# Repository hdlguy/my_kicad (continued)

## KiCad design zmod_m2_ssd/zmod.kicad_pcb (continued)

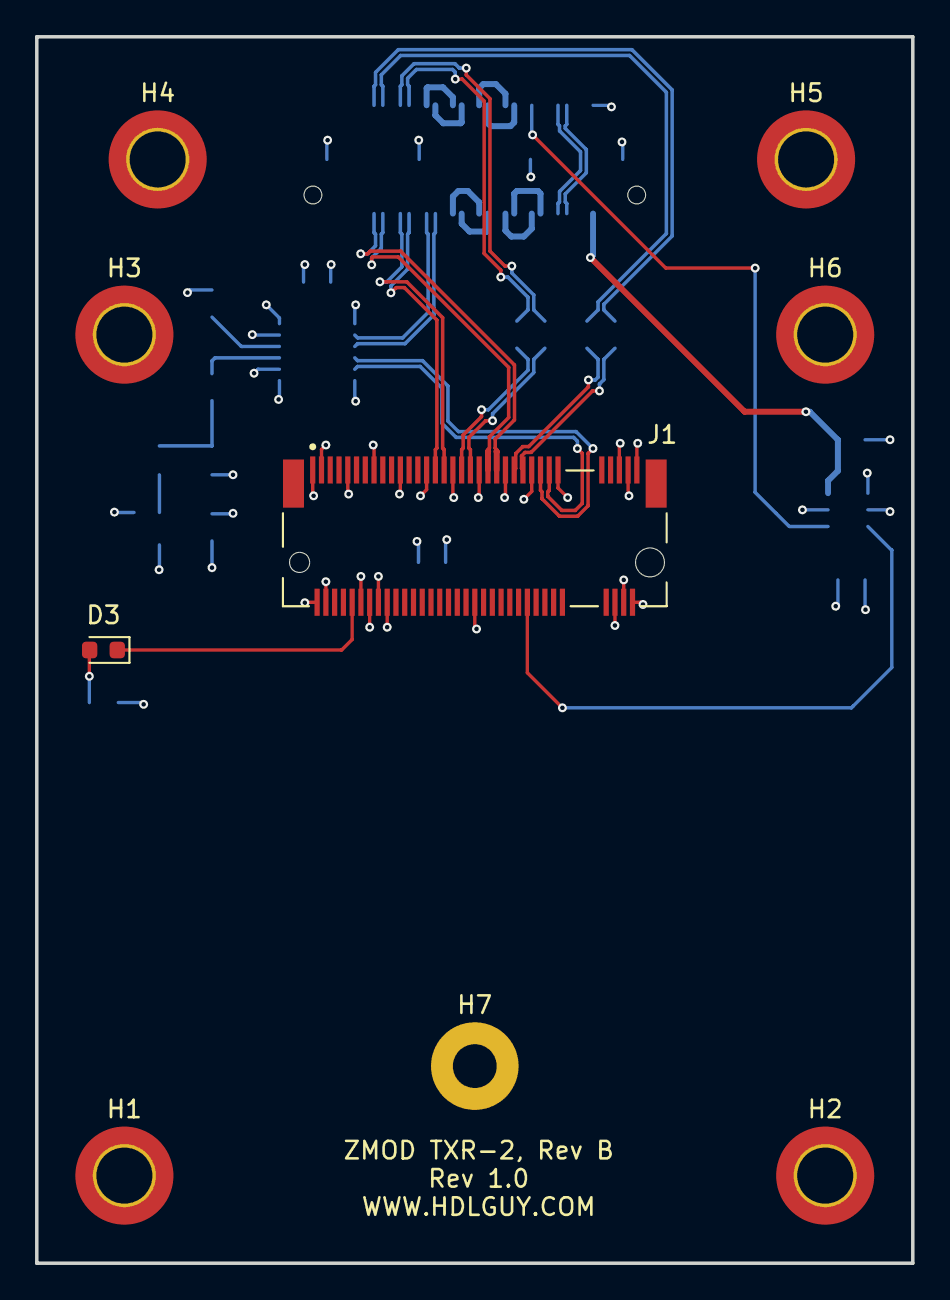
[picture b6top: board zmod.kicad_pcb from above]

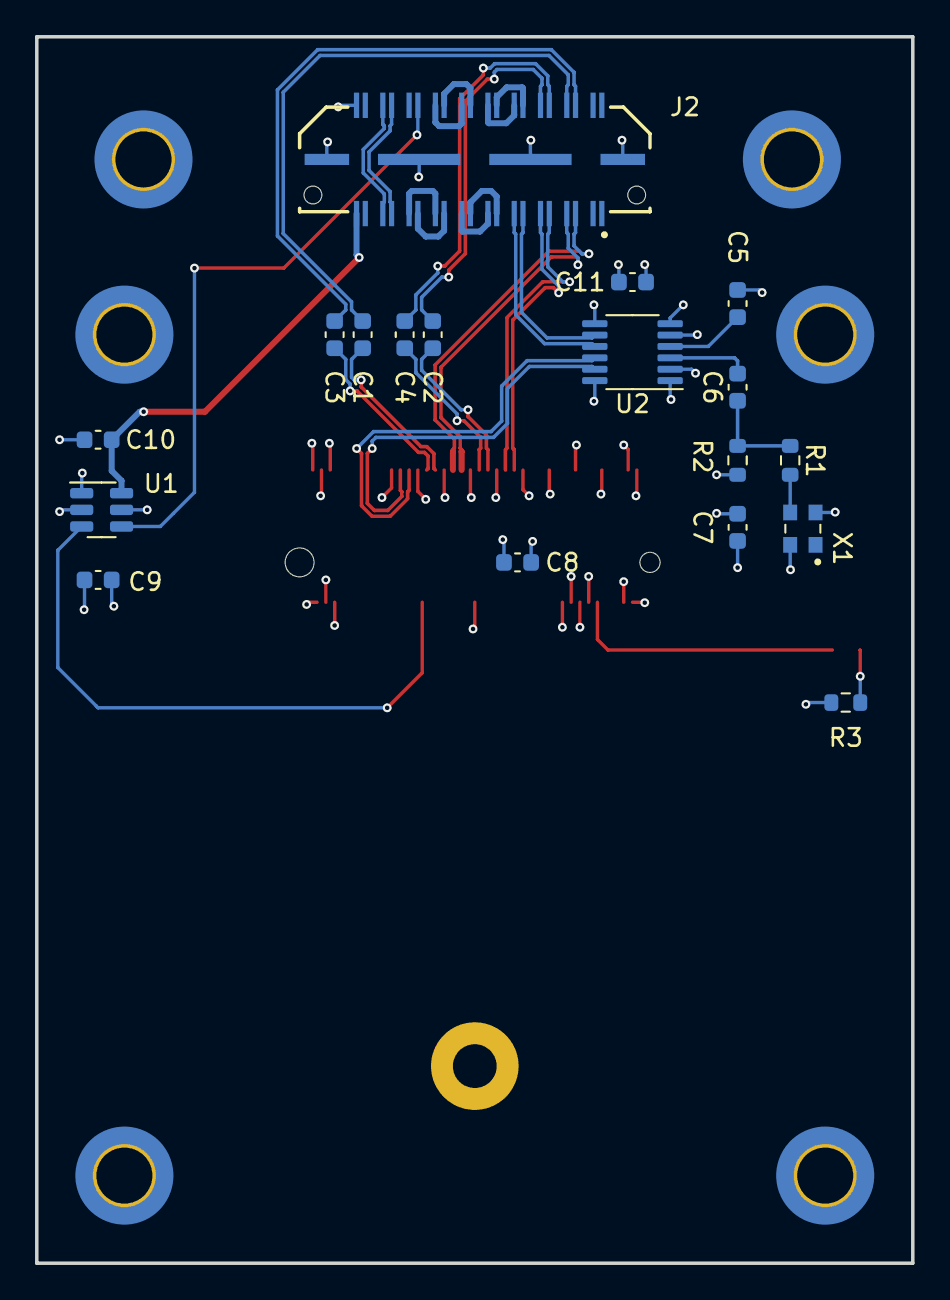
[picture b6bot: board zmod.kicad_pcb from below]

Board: 4 copper layers, 50.0 x 70.0 mm, 27 parts (18 on the bottom side), 37 nets.

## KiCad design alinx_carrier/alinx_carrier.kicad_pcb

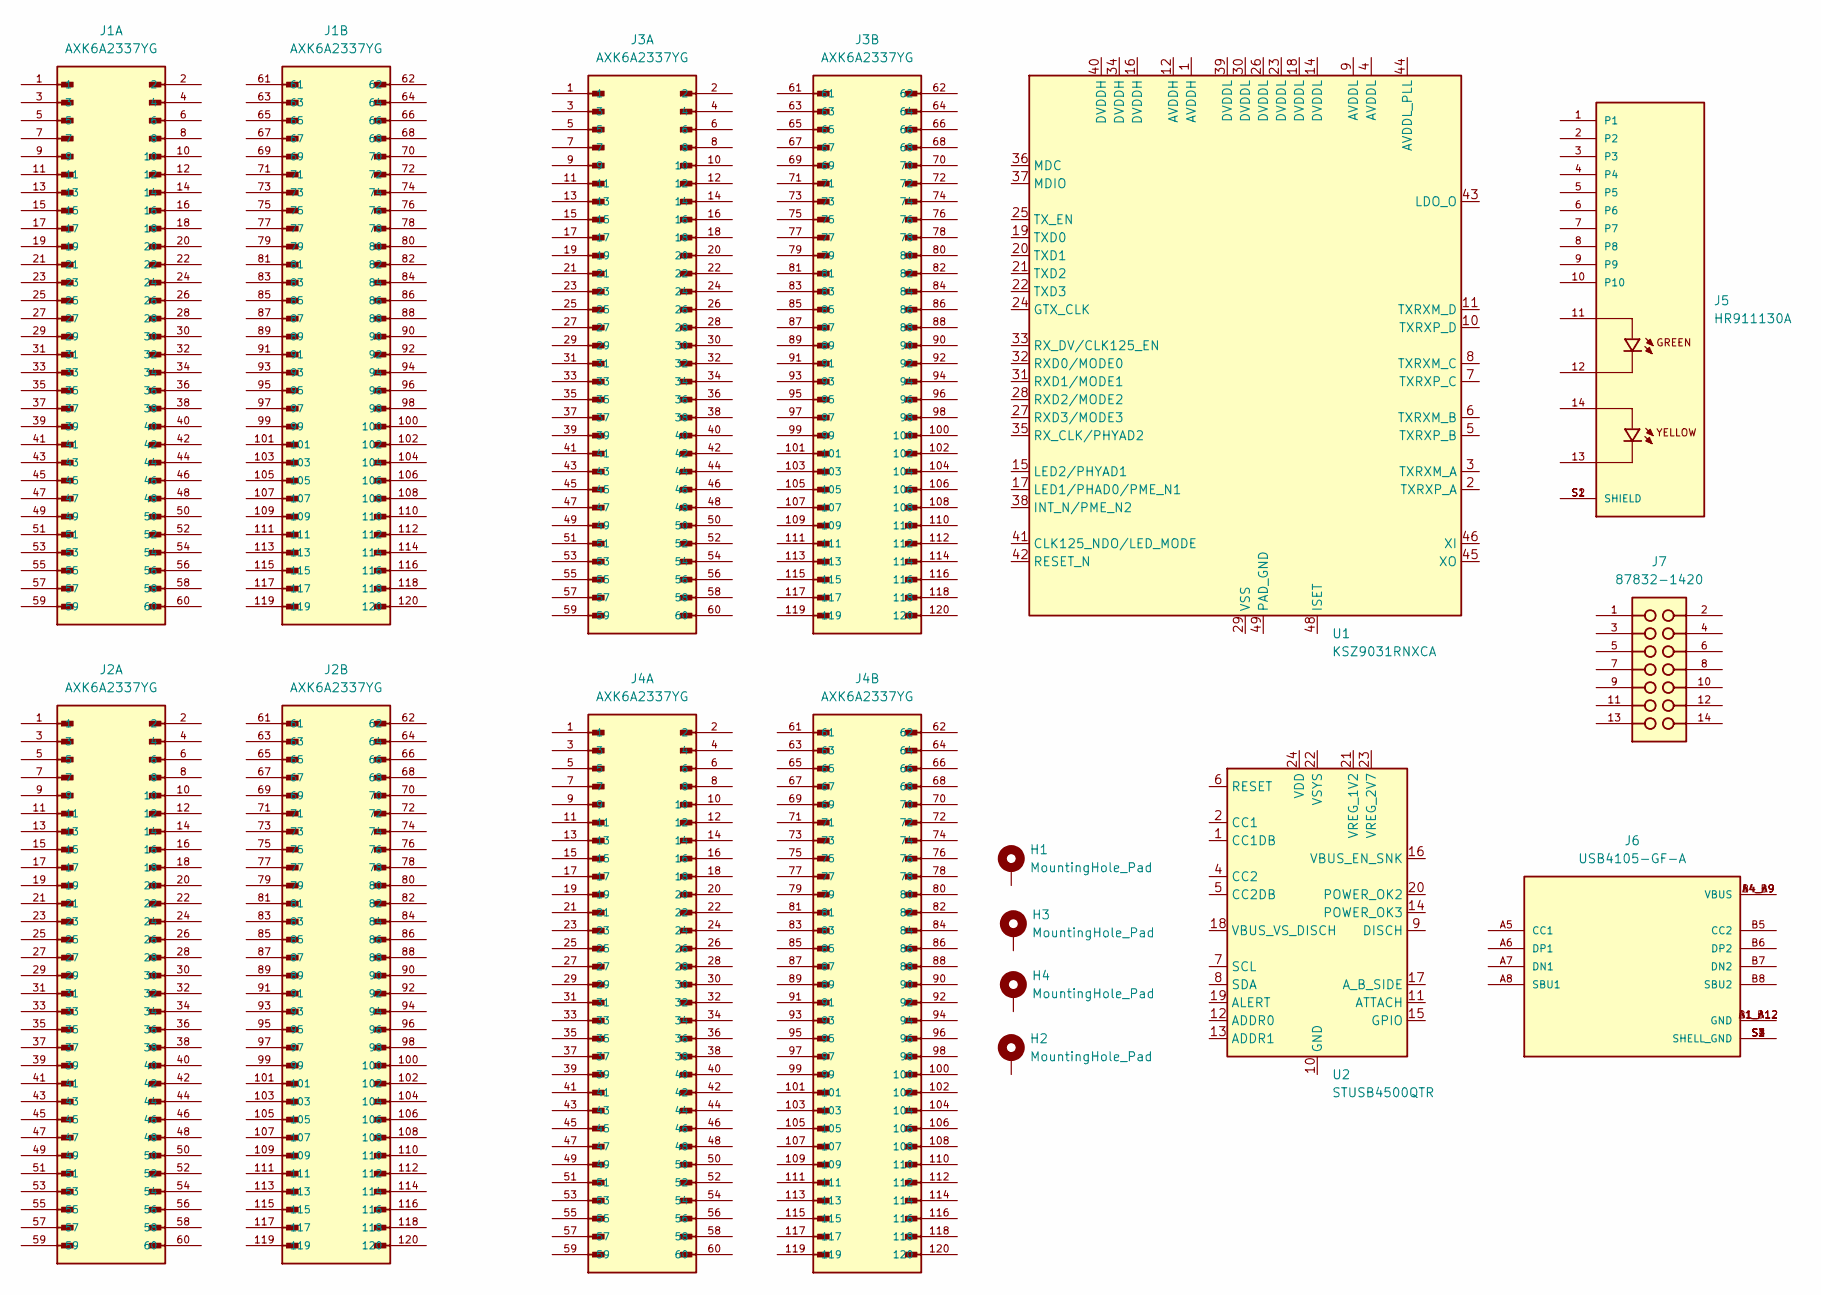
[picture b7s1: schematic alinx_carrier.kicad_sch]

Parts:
H1, H2, H3, H4: MountingHole_Pad; MountingHole_3mm_Pad_TopBottom
J1, J2, J3, J4: AXK6A2337YG; PANASONIC_AXK6A2337YG
J5: HR911130A; HANRUN_HR911130A; PARTREV A
J6: USB4105-GF-A; GCT_USB4105-GF-A; PARTREV A3
J7: 87832-1420; MOLEX_87832-1420
U1: KSZ9031RNXCA; QFN-48-1EP_7x7mm_P0.5mm_EP5.15x5.15mm
U2: STUSB4500QTR; QFN-24-1EP_4x4mm_P0.5mm_EP2.7x2.7mm

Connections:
unnamed: J5.S1 (SHIELD), J5.S2 (SHIELD)
unnamed: J6.A1_B12 (GND), J6.B1_A12 (GND)
unnamed: J6.A4_B9 (VBUS), J6.B4_A9 (VBUS)
unnamed: J6.S1 (SHELL_GND), J6.S2 (SHELL_GND), J6.S3 (SHELL_GND), J6.S4 (SHELL_GND)
unnamed: U2.10 (GND), U2.25 (GND)

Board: 2 copper layers, 13 parts (0 on the bottom side), 5 nets, no tracks yet.

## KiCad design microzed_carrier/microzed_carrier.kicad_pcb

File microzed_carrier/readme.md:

## connectors

carrier side  = 61083-101400LF - https://www.amphenol-cs.com/bergstak-61083101400lf.html

microzed side = 61082-101400LF - https://www.amphenol-cs.com/bergstak-61082101400lf.html

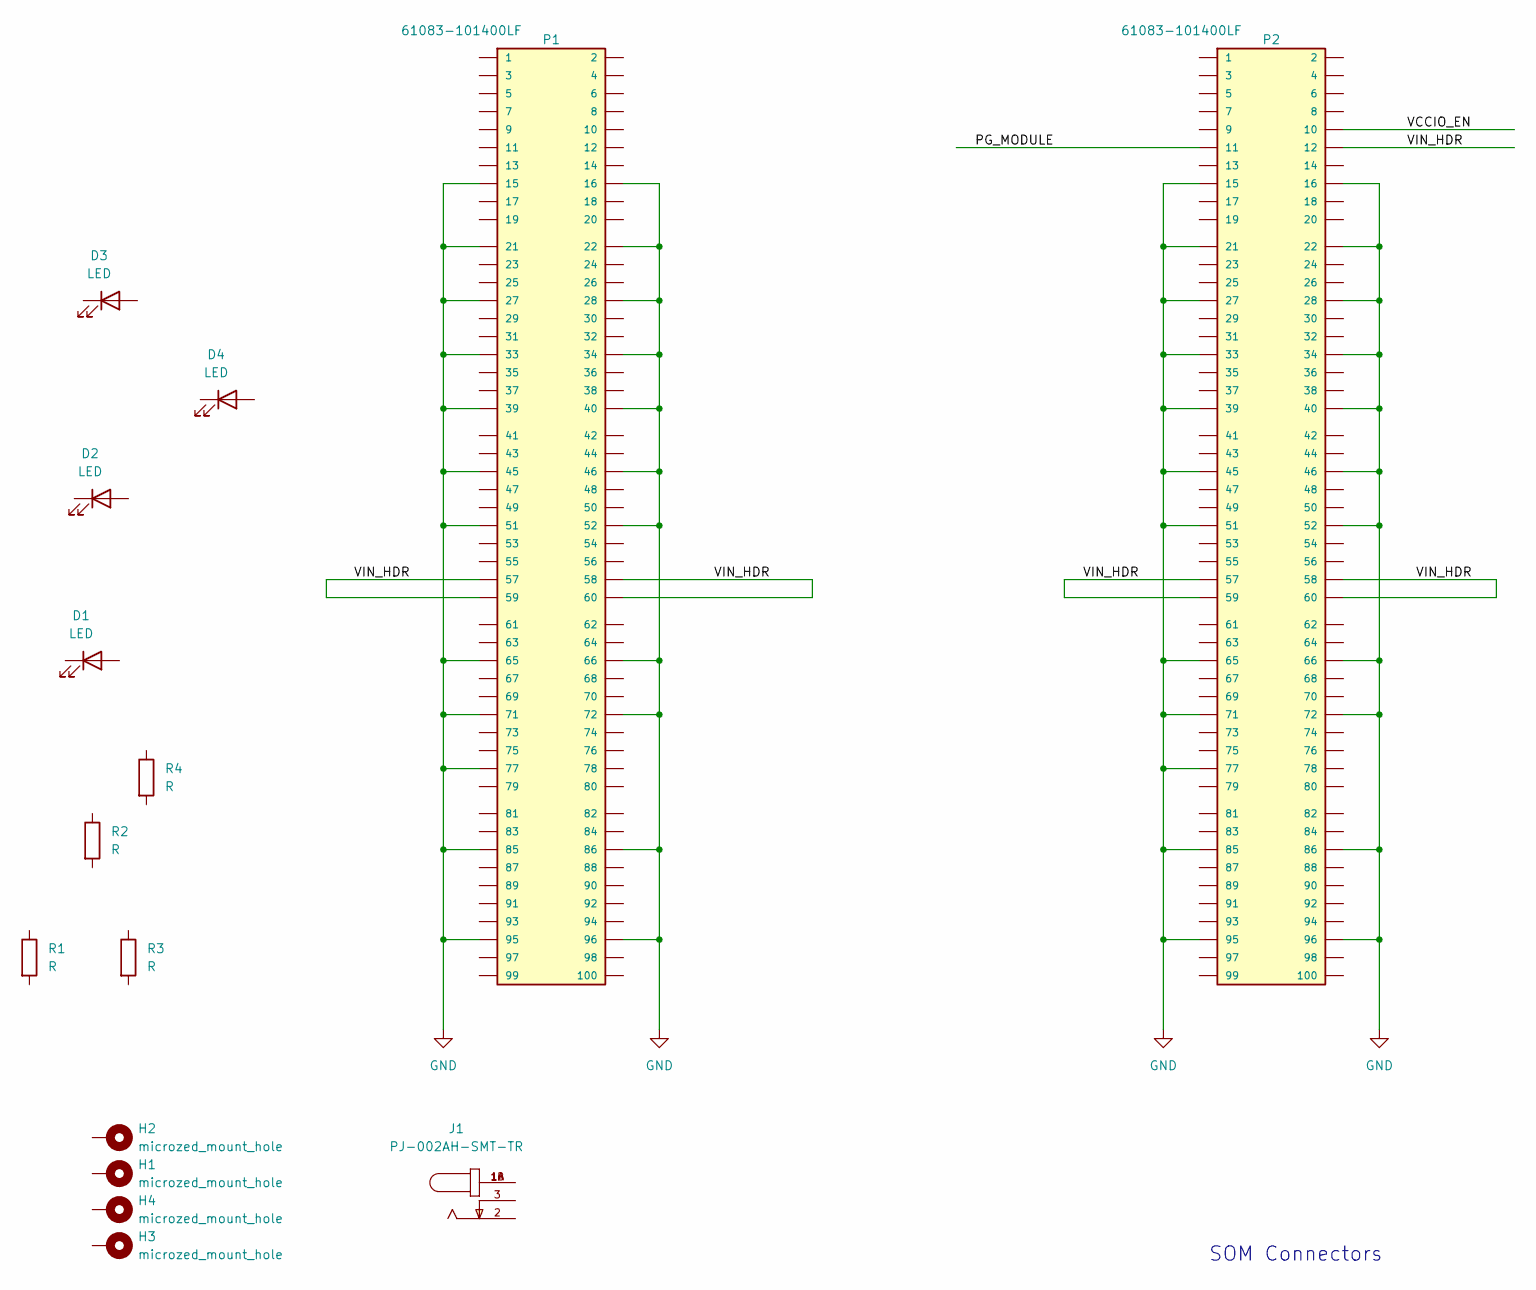
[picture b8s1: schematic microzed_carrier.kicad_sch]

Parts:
D1, D2, D3, D4: LED; LED_0603_1608Metric
H1, H2, H3, H4: microzed_mount_hole; MountingHole_3.2mm_M3_Pad
J1: PJ-002AH-SMT-TR; CUI_PJ-002AH-SMT-TR
P1, P2: 61083-101400LF; FCI_61083-101400LF
R1, R2, R3, R4: R; R_0603_1608Metric

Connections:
/PG_MODULE: P2.11
/VCCIO_EN: P2.10
/VIN_HDR: P1.57, P1.58, P1.59, P1.60, P2.12, P2.57, P2.58, P2.59, P2.60
GND: P1.15, P1.16, P1.21, P1.22, P1.27, P1.28, P1.33, P1.34, P1.39, P1.40, P1.45, P1.46, P1.51, P1.52, P1.65, P1.66, P1.71, P1.72, P1.77, P1.85, P1.86, P1.95, P1.96, P2.15, P2.16, P2.21, P2.22, P2.27, P2.28, P2.33, P2.34, P2.39, P2.40, P2.45, P2.46, P2.51, P2.52, P2.65, P2.66, P2.71, P2.72, P2.77, P2.85, P2.86, P2.95, P2.96
unnamed: J1.1A, J1.1B

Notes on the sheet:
SOM Connectors

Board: 2 copper layers, 15 parts (0 on the bottom side), 3 nets, no tracks yet.

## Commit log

2022-06-10 trying to use git on my first kicad project
2022-06-30 starting zmod design
2022-07-01 starting to route zmod diff pairs
2022-07-03 organizing
2022-07-04 added Arty FPGA design to flash the pmod LEDs
2022-07-07 fixed pmod led flasher
2022-07-07 routed zmod
2022-07-07 ready for fab, I think.
2022-07-07 adding an fpga design for the zuboard
2022-07-07 added starter fpga design for the zuboard and zmod interface
2022-07-08 cleaned up hss diff-pair
2022-07-08 organizing to start standard zmod design
2022-07-08 starting zmod standard using txr-2
2022-07-13 zmod_standard work
2022-07-13 removed redundant fill planes on zmod boards
2022-07-28 added M.2-m connector to the design for a sata ssd
2022-07-29 just a recompile to verify
2022-10-10 organizing local library files
2022-10-10 organizing local libraries, footprint and symbol
2022-10-10 organizing step files for 3D view
2022-10-15 trying again to make it so everything resolves after checkout from git
2022-10-30 trying to improve readme
2022-10-30 adjusting readme image
2022-10-30 updating image
2022-10-30 updating README.md
2022-11-12 starting project for microzed_carrier, imported symbol, footprint and 3d for SOM connector
2022-11-12 started to wire power pins on the SOM connectors
2022-11-14 added microzed outline and mounting holes
2022-11-14 added mounting holes and some LEDs
2022-11-15 committing microzed som connector footpring
2022-11-15 trying to get all the 3d paths working for microzed_carrier
2022-11-18 added CUI barrel connector for 5V power
2022-11-29 started project for alinx som carrier, requested step model for connector
2022-12-08 adding new step file created by SnapEDA
2022-12-08 pulled in latest files froms snapeda for AXK6A2337YG
2022-12-10 added mounting holes to alinx carrier
2022-12-10 located and locked mouting holes and SOM connectors
2022-12-11 created dimensioned drawing. Connector locations are questionable.
2022-12-12 adding step model for RJ45 Ethernet connector
2022-12-12 alinx carrier dimensions work
2022-12-12 microzed_carrier dimensions work
2022-12-17 Update README.md
    readme grammar fix
2022-12-19 put some usb-c stuff on the alinx carrier
2022-12-29 added jtag connector
2023-03-31 working on M.2 ZMOD board
2023-03-31 renaming the M.2 project
2023-03-31 adding clock chips for M.2
2023-04-02 added referenc oscillator and clock buffer.
2023-04-02 placed all components and locked down mounting holes and connectors, need M.2 screw hole
2023-04-02 added mounting hole for M.2 screw
2023-04-04 updating M.2 stuff
2023-04-25 first cut at routing the m.2 zmod
2023-04-26 ready to send to Oshpark
2023-04-26 updated oscilltor symbol and footprint to have 3D model
2023-06-01 starting kria carrier board design
2023-06-01 added kria connectors
2023-06-04 library paths are messed up
2023-06-04 trying to cleanup pedrolib symbol library that got switch to default ~/kicad location
2023-06-04 straitened out the pedrolib path for the kria carrier at least
2023-06-04 working on the power connections to the kria connectors. That connector will be tight to escape.
2023-06-05 starting to work power and ground planes, also kria connector fanout
2023-07-14 generated BOM
2023-07-14 Rev B of zmod M.2, changed clock buffer to give full edge rate, reduced M.2 mounting hole from 2.7 to 2.5 mm
2023-07-15 playing with connector fanout
2023-10-27 Create LICENSE
2023-12-18 updated to work with Vivado 2023.2
2024-01-03 cleanup, moved fpga work to zuboard repo
2024-01-07 readme fix
2024-01-08 starting a pcie design for an Artix fpga
2024-01-09 brought in the lucanastasio PCIe board template
2024-01-09 adding more fpga stuff
2024-01-09 tweaks, thinking about it some more
2024-01-14 looking at Xilinx Artix Ultrascale+ for pcie board
2024-01-14 copying in PCIe symbols, footprints and 3D
2024-01-14 x8 PCIe connector
2024-01-15 changed out Artix-7 for Artix-UP
2024-01-15 added PMOD and JTAG connectors
2024-01-15 wired pcie links with ac coupling caps
2024-01-15 pcie lanes need to be swapped I think.
2024-01-15 swapped the pcie lanes for routing
2024-01-19 starting an x1 pcie design to plug into the CM4 io board
2024-01-22 working on x1 pcie card
2024-02-05 set 3D for xilinx bga676
2024-03-11 starting custom carrier for custom artix fpga module
2024-03-12 working on custom carrier in V7
2024-03-13 added ribbon cable connectors
2024-03-13 added 3M connector
2024-03-15 working on high-speed cables.
2024-03-16 tuned diff lengths and adjusted annular rings
2024-03-17 improved 3d model for 3M connector
2024-03-18 still looking at 3M connector pinout
2024-03-18 slight cleanup
2024-03-19 rewired 3M connectors to recommended diff pair arrangement. tuned diff pair skews.
2024-03-20 custom_carrier upgraded to Kicad 8.0
2024-03-20 added LED's
2024-03-20 cleanup for kicad 8
2024-03-21 looking at top and bottom ground fills
2024-03-21 as ordered from OshPark
2024-03-21 adding BOM
2024-03-22 fixed 3D paths for jtag and power connectors
2024-03-27 fixed loopback wiring error, increased Revision from A-1 to B-1
2024-03-27 Rev B-1 with proper loopback pinout routed
2024-03-28 tuned loopback diff lengths
2024-04-11 changed top and bottom pour clearance not to affect impedance
2024-08-05 added annotation to schematic for J3 that really isn't needed
2024-09-10 starting mini keyboard experiments
2024-09-10 adding key switches
2024-09-10 adding more keys and looking at spacing
2024-09-11 updating library for keyboard work
2024-09-11 library update for keyboard
2024-09-12 added Teensy 4.0
2024-09-12 added a little Teensy project to emulate a keyboard
2024-09-13 adding a teensy blinker
2024-09-14 Looking at Arduino 33 IOT for CPU to get arduino-cli support
2024-09-15 starting to work with the arduion-cli
2024-09-16 trying to work with Nano 33 IoT
2024-09-18 arduino-cli compiles and uploads. need Makefile
2024-09-18 created Makefile for blink
2024-09-18 Makefile cleanup
2024-09-19 prepping to wire the switches and diodes to the array
2024-09-19 initial placement of all diodes
2024-09-20 starting OpensCAD top_frame design
2024-09-20 added details to 3D frame
2024-09-20 fiddling
2024-09-24 fiddling with key locations in top_frame.scad, still not right
2024-09-25 moved kicad stuff to subfolder
2024-09-25 rotated key switches 180 degreees
2024-09-25 looking at PG151101S11 socket for MX switches.
2024-09-25 cleaned up table of key cutouts on top_frame.scad
2024-09-26 arduino cleanup
2024-09-26 added serial console
2025-11-18 pmod_test to kicad 9
